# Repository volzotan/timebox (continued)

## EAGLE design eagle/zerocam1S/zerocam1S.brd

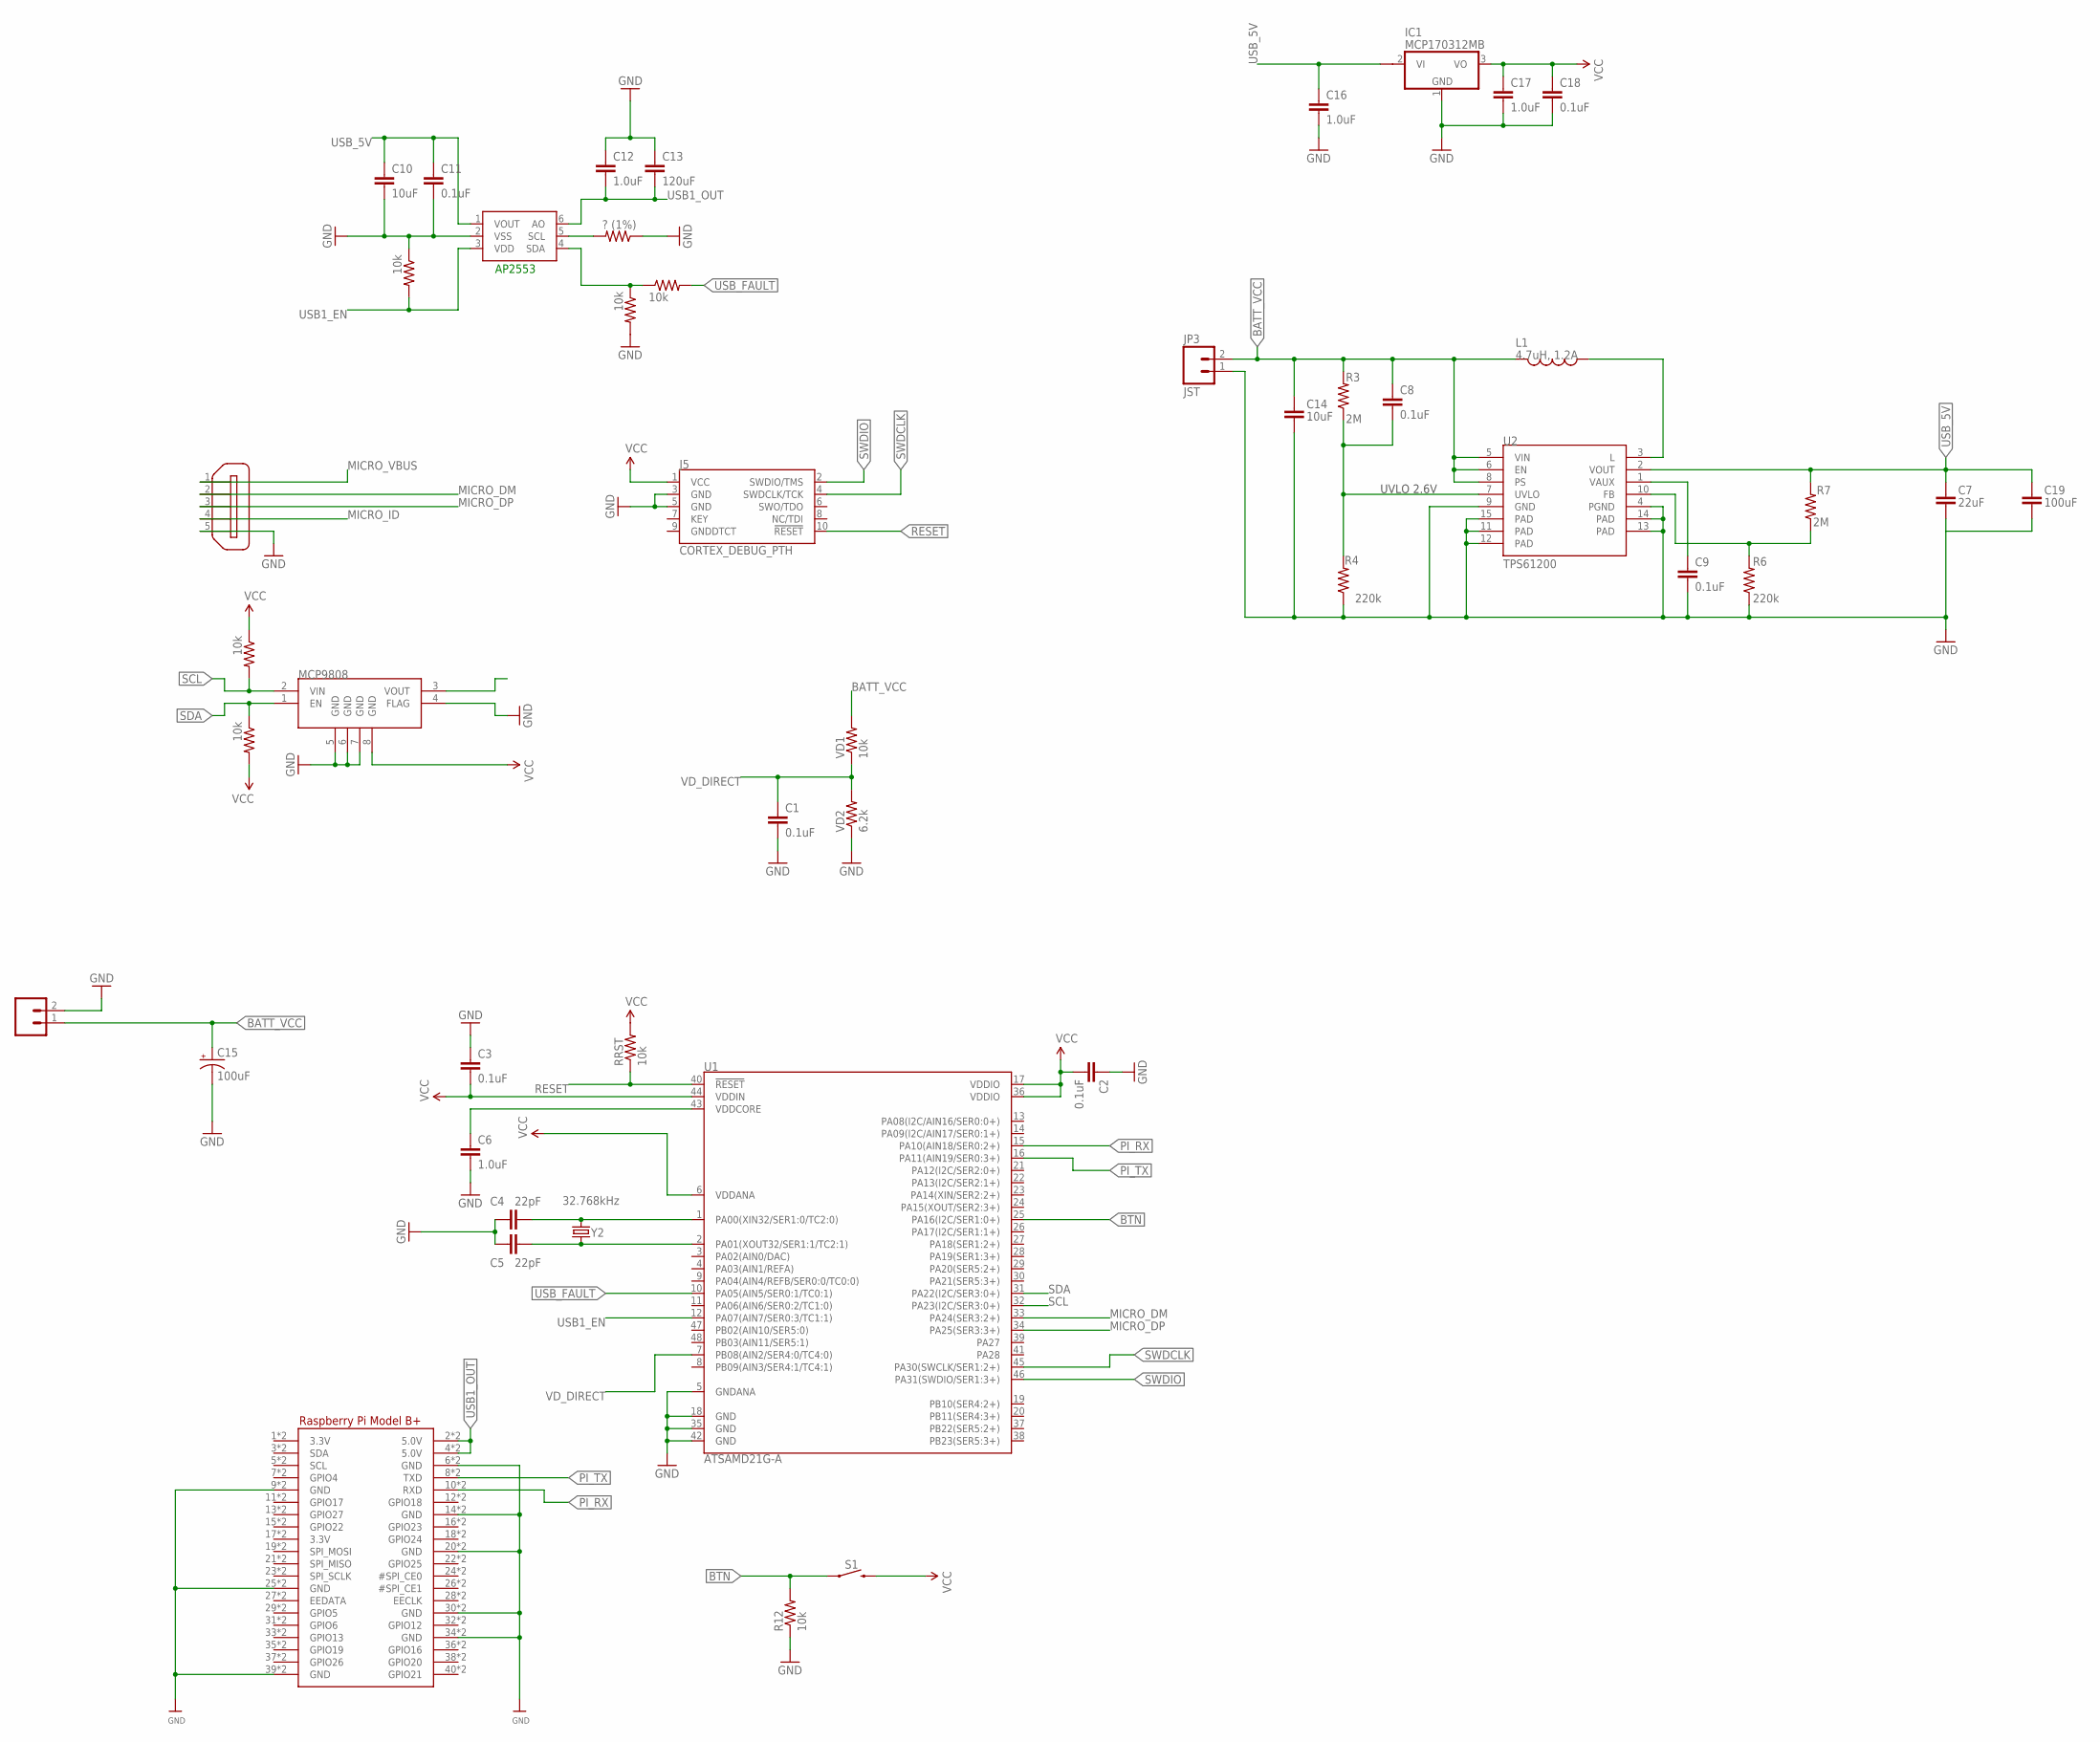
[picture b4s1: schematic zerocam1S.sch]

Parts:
AP2553: MCP4725; SOT23-6
C1, C2, C3, C8, C9, C11, C18: 0.1uF; 0805
C4, C5: 22pF; 0805
C6, C16: 1.0uF; 0805
C7: 22uF; 0805
C10: 10uF; 0805
C12, C17: 1.0uF; 1206
C13: 120uF; 1206
C14: 10uF; 1206
C15: 100uF; PANASONIC_D
C19: 100uF; 1206
IC1: MCP170312MB; SOT89
J1: CONN_023.5MM-NO_SILK; SCREWTERMINAL-3.5MM-2-NS
J5: CORTEX_DEBUG_PTH; 2X5-PTH-1.27MM
JP3: JST; JST-2-SMD
L1: 4.7uH, 1.2A; CDRH2D09
MCP9808: V_REG_MIC5216; MSOP8
R3, R7: 2M; 0805
R4, R6: 220k; 0805
R12: 10k; 0805
RPI1: RASPBERRYPI_BPLUS_BONNET_THMSMT; PI_BONNET_THMSMT
RRST: 10k; 0805
R_I2C_1, R_I2C_2: 10k; 0805
R_MOSFET_USB1: ? (1%); 0805
R_MOSFET_USB2, R_MOSFET_USB3, R_MOSFET_USB4: 10k; 0805
S1: MOMENTARY-SWITCH-SPST-SMD-5.2-REDUNDANT; TACTILE_SWITCH_SMD_5.2MM
U1: ATSAMD21G-A; TQFP-48
U2: TPS61200; QFN-10_PAD
VD1: 10k; 0805
VD2: 6.2k; 0805
X2: ZX62D-B-5PA8
Y2: 32.768kHz; CRYSTAL-SMD-3.2X1.5MM

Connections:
BATT_VCC: C8.1, C14.1, C15.+, J1.1, JP3.2, L1.P$2 (2), R3.2, U2.5 (VIN), U2.6 (EN), U2.8 (PS), VD1.2
BTN: R12.2, S1.1, S1.2 (1), U1.25 (PA16(I2C/SER1:0+))
FB: R6.2, R7.1, U2.10 (FB)
GND: AP2553.2 (VSS), C1.2, C2.1, C3.1, C4.1, C5.1, C6.2, C7.2, C9.2, C10.2, C11.2, C12.1, C13.1, C14.2, C15.-, C16.2, C17.2, C18.2, C19.2, IC1.1 (GND), J1.2, J5.3 (GND), J5.5 (GND), JP3.1, MCP9808.4 (FLAG), MCP9808.5 (GND), MCP9808.6 (GND), MCP9808.7 (GND), R4.1, R6.1, R12.1, RPI1.6 (GND), RPI1.9 (GND), RPI1.14 (GND), RPI1.20 (GND), RPI1.25 (GND), RPI1.30 (GND), RPI1.34 (GND), RPI1.39 (GND), RPI1.S6 (GND), RPI1.S9 (GND), RPI1.S14 (GND), RPI1.S20 (GND), RPI1.S25 (GND), RPI1.S30 (GND), RPI1.S34 (GND), RPI1.S39 (GND), R_MOSFET_USB1.1, R_MOSFET_USB2.2, R_MOSFET_USB3.1, U1.5 (GNDANA), U1.18 (GND), U1.35 (GND), U1.42 (GND), U2.4 (PGND), U2.9 (GND), U2.11 (PAD), U2.12 (PAD), U2.13 (PAD), U2.14 (PAD), U2.15 (PAD), VD2.1, X2.5
MICRO_DM: U1.33 (PA24(SER3:2+)), X2.2
MICRO_DP: U1.34 (PA25(SER3:3+)), X2.3
MICRO_ID: X2.4
MICRO_VBUS: X2.1
unnamed: C6.1, U1.43 (VDDCORE)
unnamed: L1.P$1 (1), U2.3 (L)
unnamed: AP2553.5 (SCL), R_MOSFET_USB1.2
unnamed: AP2553.4 (SDA), R_MOSFET_USB2.1, R_MOSFET_USB4.1
unnamed: C9.1, U2.1 (VAUX)
unnamed: C4.2, U1.1 (PA00(XIN32/SER1:0/TC2:0)), Y2.P$2 (2)
unnamed: C5.2, U1.2 (PA01(XOUT32/SER1:1/TC2:1)), Y2.P$1 (1)
PI_RX: RPI1.10 (RXD), RPI1.S10 (RXD), U1.15 (PA10(AIN18/SER0:2+))
PI_TX: RPI1.8 (TXD), RPI1.S8 (TXD), U1.16 (PA11(AIN19/SER0:3+))
RESET: J5.10 (!RESET), RRST.1, U1.40 (!RESET!)
SCL: MCP9808.2 (VIN), R_I2C_1.2, U1.32 (PA23(I2C/SER3:0+))
SDA: MCP9808.1 (EN), R_I2C_2.1, U1.31 (PA22(I2C/SER3:0+))
SWDCLK: J5.4 (SWDCLK/TCK), U1.45 (PA30(SWCLK/SER1:2+))
SWDIO: J5.2 (SWDIO/TMS), U1.46 (PA31(SWDIO/SER1:3+))
USB1_EN: AP2553.3 (VDD), R_MOSFET_USB3.2, U1.12 (PA07(AIN7/SER0:3/TC1:1))
USB1_OUT: AP2553.6 (AO), C12.2, C13.2, RPI1.2 (5.0V), RPI1.4 (5.0V), RPI1.S2 (5.0V), RPI1.S4 (5.0V)
USB_5V: AP2553.1 (VOUT), C7.1, C10.1, C11.1, C16.1, C19.1, IC1.2@1 (VI1), R7.2, U2.2 (VOUT)
USB_FAULT: R_MOSFET_USB4.2, U1.10 (PA05(AIN5/SER0:1/TC0:1))
UVLO: C8.2, R3.1, R4.2, U2.7 (UVLO)
VCC: C2.2, C3.2, C17.1, C18.1, IC1.3 (VO), J5.1 (VCC), MCP9808.8 (GND), RRST.2, R_I2C_1.1, R_I2C_2.2, S1.3 (2), S1.4 (2), U1.6 (VDDANA), U1.17 (VDDIO), U1.36 (VDDIO), U1.44 (VDDIN)
VD_DIRECT: C1.1, U1.7 (PB08(AIN2/SER4:0/TC4:0)), VD1.1, VD2.2

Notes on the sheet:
AP2553
UVLO 2.6V

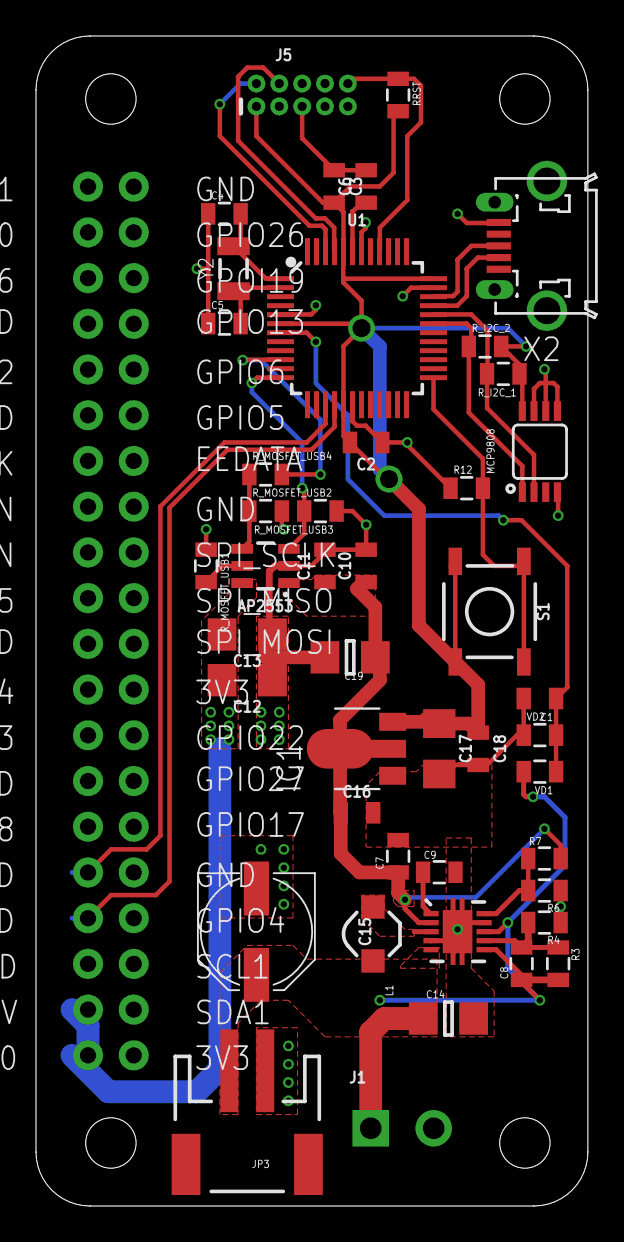
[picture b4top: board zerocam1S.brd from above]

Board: 2 copper layers, 30.7 x 65.0 mm, 46 parts (0 on the bottom side), 27 nets.

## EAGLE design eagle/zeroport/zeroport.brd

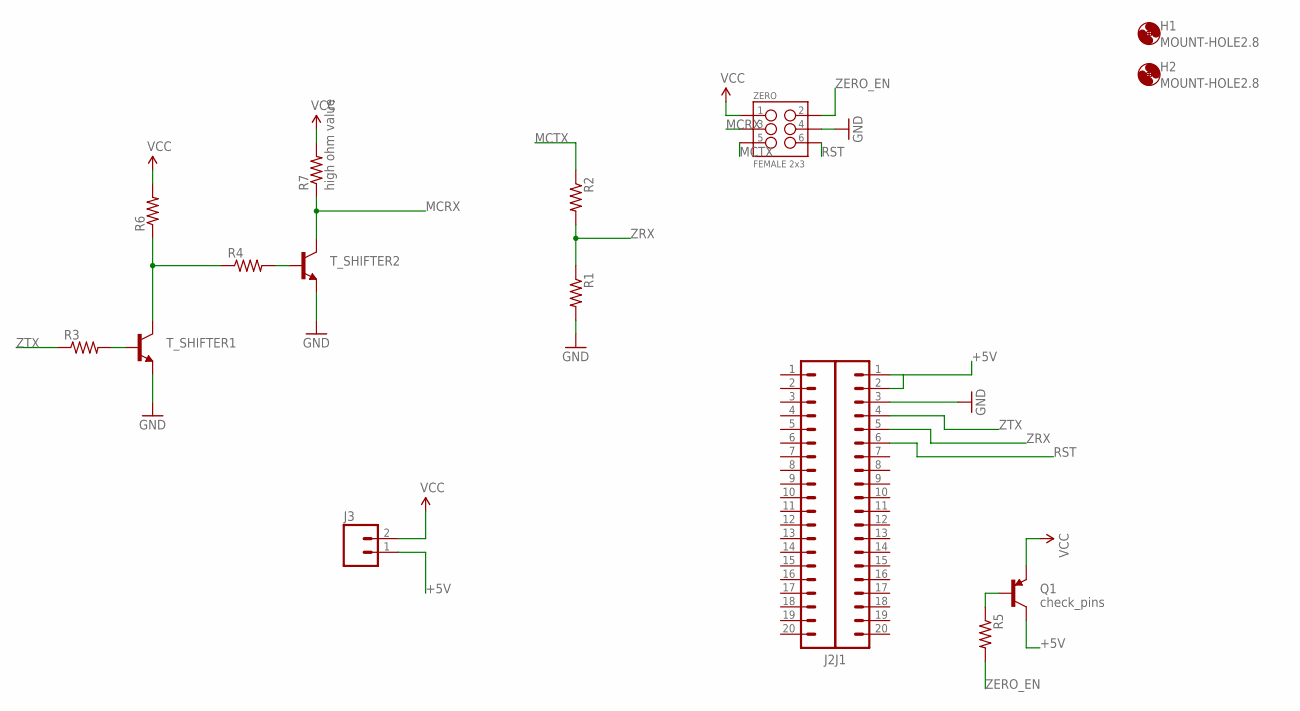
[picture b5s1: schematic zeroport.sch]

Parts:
H1, H2: MOUNT-HOLE2.8; 2,8
J1, J2: M20LOCK; 1X20_LOCK
J3: M02LOCK; 1X02_LOCK
Q1: check_pins; TO-92
R1, R2, R3, R4, R5, R6: RESISTORPTH-1/4W; AXIAL-0.4
R7: high ohm value; AXIAL-0.4
T_SHIFTER1, T_SHIFTER2: TRANSISTOR_NPN2N3904; TO-92
ZERO: FEMALE 2x3; 2X3

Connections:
+5V: J1.1, J3.1, Q1.3 (C)
GND: J1.3, R1.P$2 (2), T_SHIFTER1.1 (E), T_SHIFTER2.1 (E), ZERO.4
MCRX: R7.P$1 (1), T_SHIFTER2.3 (C), ZERO.3
MCTX: R2.P$1 (1), ZERO.5
unnamed: Q1.2 (B), R5.P$1 (1)
unnamed: R3.P$2 (2), T_SHIFTER1.2 (B)
unnamed: R4.P$1 (1), R6.P$1 (1), T_SHIFTER1.3 (C)
unnamed: R4.P$2 (2), T_SHIFTER2.2 (B)
RST: J1.6, ZERO.6
VCC: J3.2, Q1.1 (E), R6.P$2 (2), R7.P$2 (2), ZERO.1
ZERO_EN: R5.P$2 (2), ZERO.2
ZRX: J1.5, R1.P$1 (1), R2.P$2 (2)
ZTX: J1.4, R3.P$1 (1)

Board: 2 copper layers, 16 parts (0 on the bottom side), 13 nets, no tracks yet.
